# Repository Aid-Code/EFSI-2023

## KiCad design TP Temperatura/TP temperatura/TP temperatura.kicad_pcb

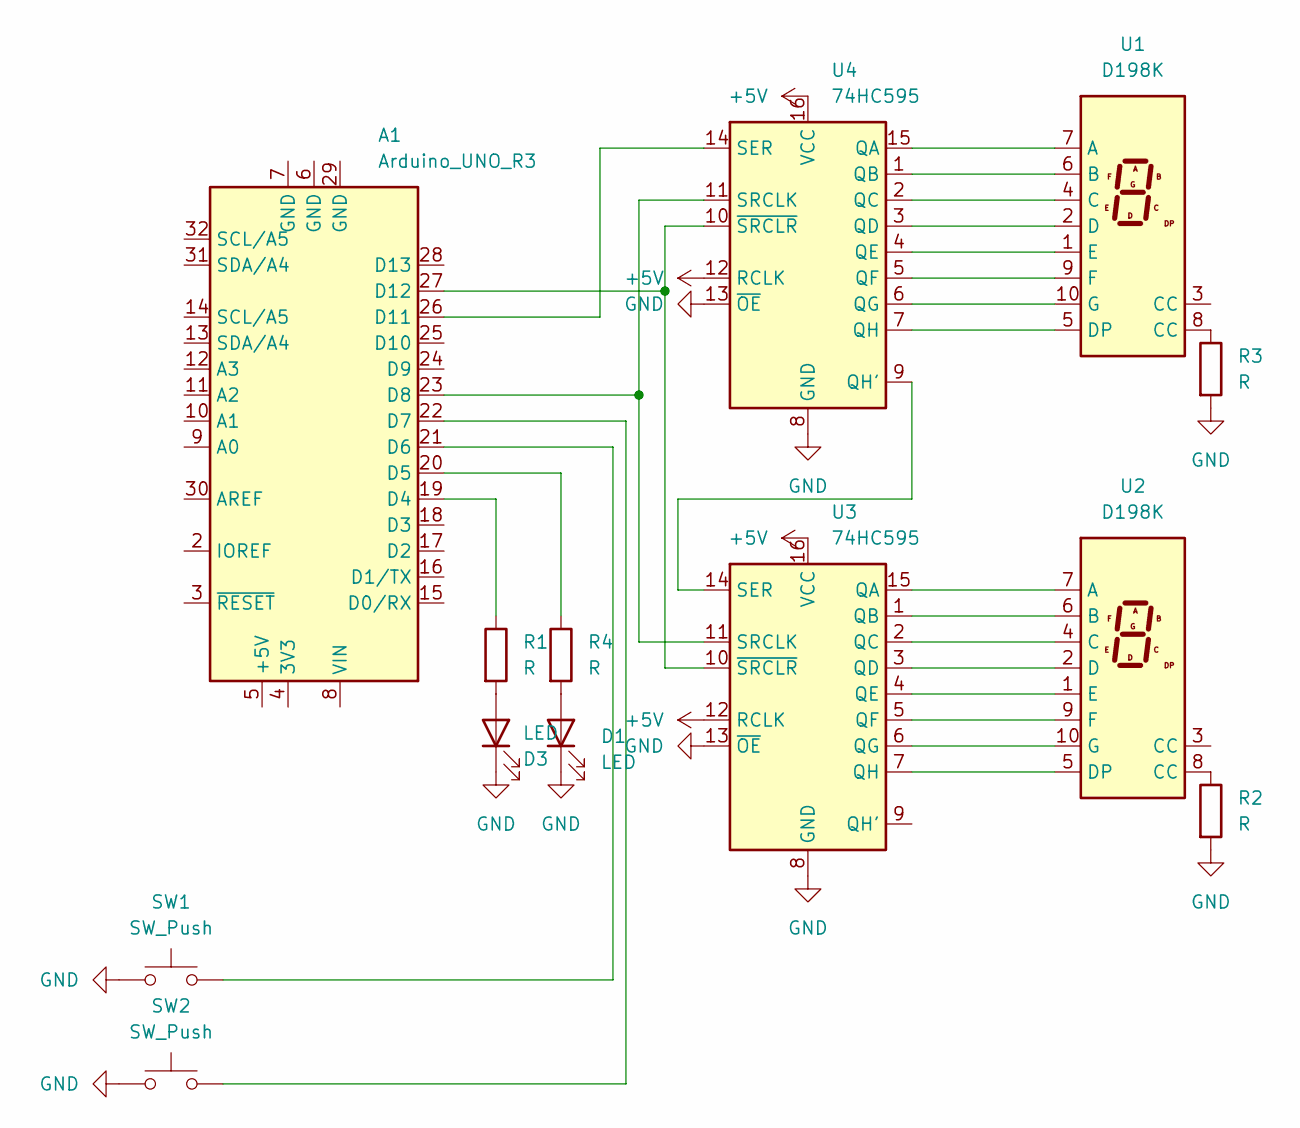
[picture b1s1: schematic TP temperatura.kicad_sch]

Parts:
A1: Arduino_UNO_R3
D1, D3: LED; LED_D5.0mm
R1, R2, R3, R4: R; R_Axial_DIN0204_L3.6mm_D1.6mm_P5.08mm_Horizontal
SW1, SW2: SW_Push; SW_PUSH_6mm
U1, U2: D198K; D1X8K
U3, U4: 74HC595; DIP-16_W7.62mm_LongPads

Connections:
+5V: U3.12 (RCLK), U3.16 (VCC), U4.12 (RCLK), U4.16 (VCC)
GND: D1.1 (K), D3.1 (K), R2.2, R3.2, SW1.1, SW2.1, U3.8 (GND), U3.13 (~OE), U4.8 (GND), U4.13 (~OE)
unnamed: A1.19 (D4), R1.1
unnamed: A1.20 (D5), R4.1
unnamed: A1.21 (D6), SW1.2
unnamed: A1.22 (D7), SW2.2
unnamed: A1.23 (D8), U3.11 (SRCLK), U4.11 (SRCLK)
unnamed: A1.26 (D11), U4.14 (SER)
unnamed: A1.27 (D12), U3.10 (~SRCLR), U4.10 (~SRCLR)
unnamed: D1.2 (A), R4.2
unnamed: D3.2 (A), R1.2
unnamed: R2.1, U2.8 (CC)
unnamed: R3.1, U1.8 (CC)
unnamed: U1.7 (A), U4.15 (QA)
unnamed: U1.6 (B), U4.1 (QB)
unnamed: U1.4 (C), U4.2 (QC)
unnamed: U1.2 (D), U4.3 (QD)
unnamed: U1.5 (DP), U4.7 (QH)
unnamed: U1.1 (E), U4.4 (QE)
unnamed: U1.9 (F), U4.5 (QF)
unnamed: U1.10 (G), U4.6 (QG)
unnamed: U2.7 (A), U3.15 (QA)
unnamed: U2.6 (B), U3.1 (QB)
unnamed: U2.4 (C), U3.2 (QC)
unnamed: U2.2 (D), U3.3 (QD)
unnamed: U2.5 (DP), U3.7 (QH)
unnamed: U2.1 (E), U3.4 (QE)
unnamed: U2.9 (F), U3.5 (QF)
unnamed: U2.10 (G), U3.6 (QG)
unnamed: U3.14 (SER), U4.9 (QH')

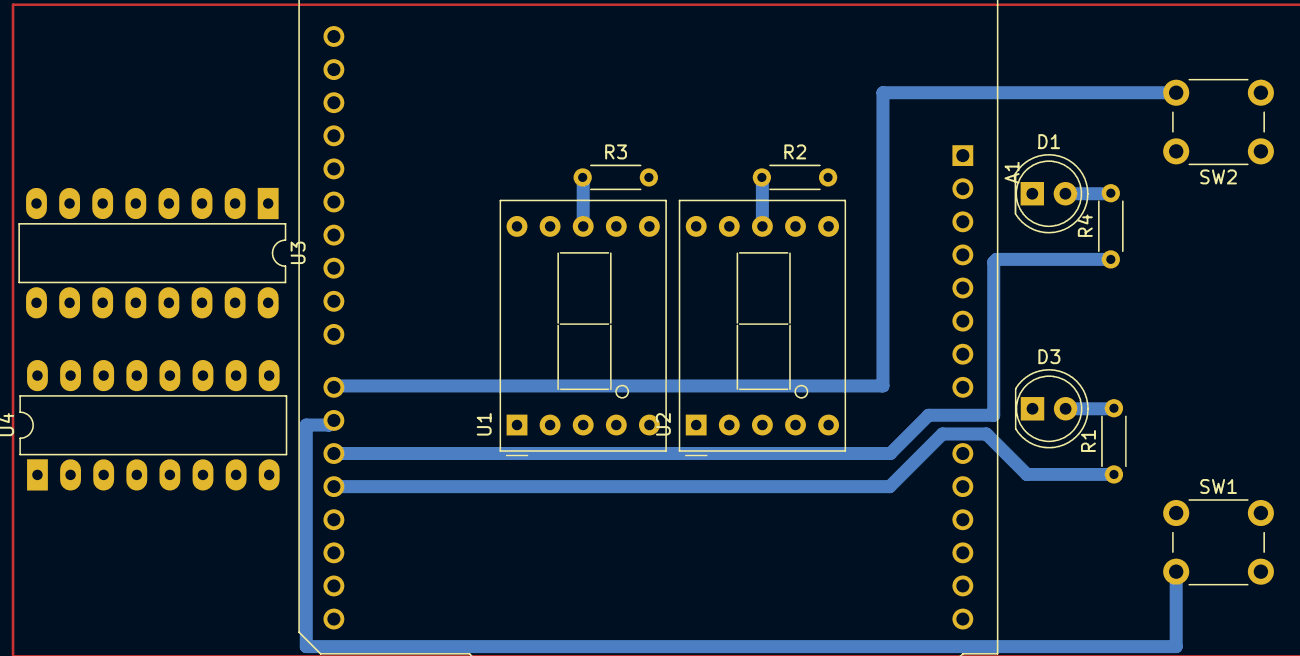
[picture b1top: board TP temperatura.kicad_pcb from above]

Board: 2 copper layers, 13 parts (0 on the bottom side), 30 nets.

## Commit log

2023-10-23 TP Temperatura
